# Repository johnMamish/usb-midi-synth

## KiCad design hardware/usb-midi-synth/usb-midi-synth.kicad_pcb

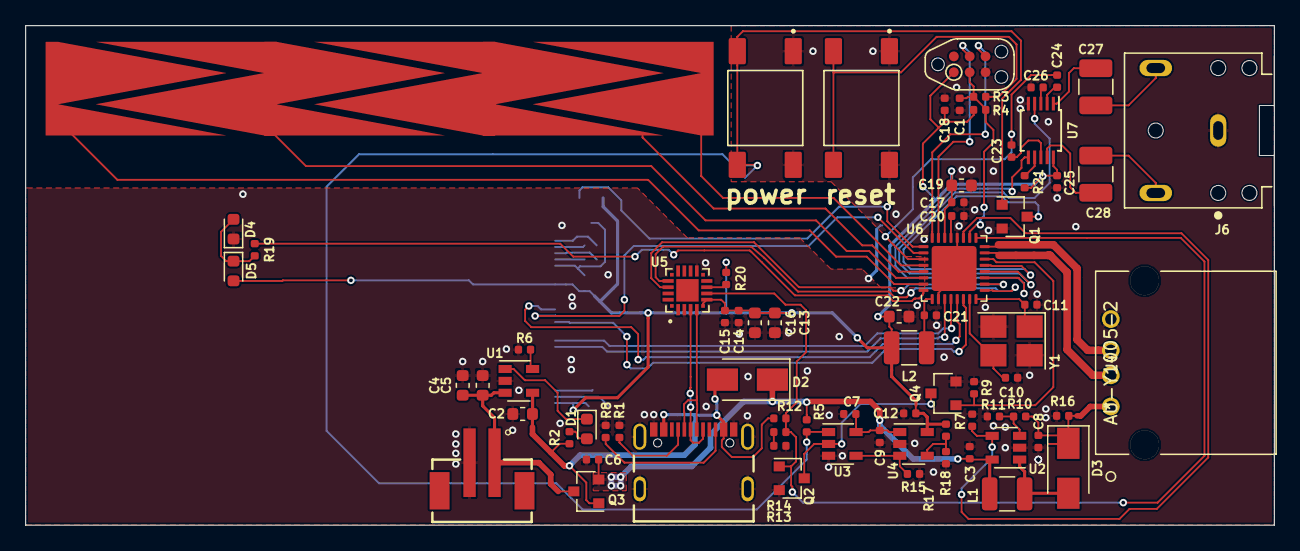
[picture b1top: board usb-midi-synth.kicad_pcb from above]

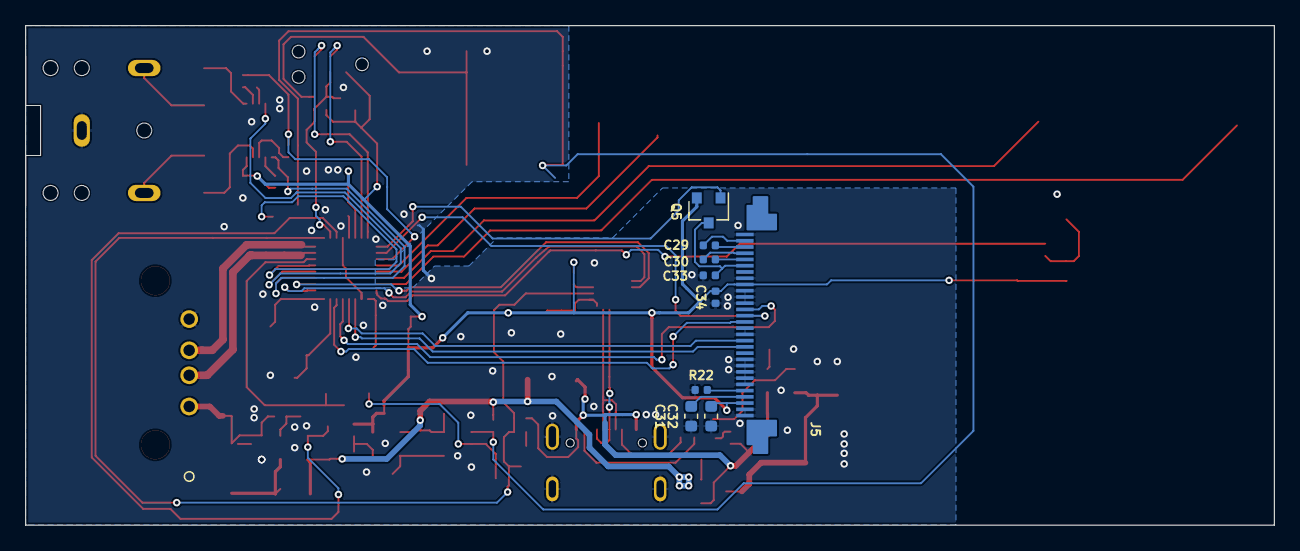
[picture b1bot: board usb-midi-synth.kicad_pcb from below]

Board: 2 copper layers, 100.0 x 40.0 mm, 85 parts (9 on the bottom side), 67 nets.

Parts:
C1, C7, C14, C15, C17, C18, C21: 100n; C_0402_1005Metric
C2, C4, C5, C13, C16, C31: 4.7u; C_0603_1608Metric
C3, C6, C8, C9, C10, C11, C12, C20, C25, C26, C29, C30, C33, C34: 1u; C_0402_1005Metric
C19, C22: 10u; C_0603_1608Metric
C23, C24: 0.47u; C_0402_1005Metric
C27, C28: 47u; C_1210_3225Metric_Pad1.42x2.65mm_HandSolder
C32: 2.2u; C_0603_1608Metric
D1, D4, D5: LED_Small; LED_0603_1608Metric
D2, D3: D; D_SMA
J1: USB4105-GF-A; GCT_USB4105-GF-A
J2: B2B-PH-SM4-TB(LF)(SN); JST_B2B-PH-SM4-TB(LF)(SN)
J3: TC2030-CTX; TC2030-IDC-NL
J4: AU-Y1005-2
J5: Conn_01x30; SFV30R-4STE1HLF
J6: SJ1-3523N; CUI_SJ1-3523N
L1, L2: 10u; L_1210_3225Metric
Q1, Q2, Q4: 2N7002; SOT-23
Q3, Q5: Q_PMOS_GSD; SOT-23
R1, R8: 5.1k; R_0402_1005Metric
R2, R3, R19: 100; R_0402_1005Metric
R4, R5, R7, R9, R11, R12, R13, R14, R15, R18, R20, R21: 10k; R_0402_1005Metric
R6, R16: 2k; R_0402_1005Metric
R10, R17: 30k; R_0402_1005Metric
R22: 390k; R_0402_1005Metric
SW1, SW2: FSM4JSMA; TE_FSM4JSMA
U1: MCP73831-2; SOT-23-5
U2: AP3012K; SOT-23-5
U3: 74AHC1G00; SOT-23-5
U4: ap7366-w5; SOT-23-5
U5: cp2102n-gqfn20; IC_CP2102N-A01-GQFN20
U6: ATSAMD21E18A-M; QFN-32-1EP_5x5mm_P0.5mm_EP3.6x3.6mm
U7: LM4811; TSSOP-10_3x3mm_P0.5mm
UI1: touch-strip; touch-slider-4
Y1: Crystal_GND24; Crystal_SMD_3225-4Pin_3.2x2.5mm_HandSoldering

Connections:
D+_host: J4.3, U6.24
D-_host: J4.2, U6.23
DAC_out: C23.2, C24.2, U6.3
GND: C1.2, C2.2, C3.2, C4.2, C5.2, C6.2, C7.2, C8.2, C9.2, C10.1, C11.1, C12.2, C13.1, C14.1, C15.1, C16.1, C17.2, C18.2, C19.2, C20.1, C21.2, C22.2, C25.1, C26.2, C31.1, C32.1, C33.1, C34.1, D4.1, J1.A1_B12, J1.B1_A12, J1.S1, J1.S2, J1.S3, J1.S4, J2.2, J3.5, J4.4, J5.1, J5.2, J5.6, J5.7, J5.8, J5.9, J5.10, J5.14, J5.15, J5.19, J5.20, J5.21, J5.23, J5.30, J6.1, Q1.2, Q2.2, Q4.2, R1.2, R6.2, R7.2, R8.2, R9.2, R11.2, R14.2, R15.2, R16.1, R18.2, R22.2, SW1.1, SW1.2, SW2.1, SW2.2, U1.2, U2.2, U3.3, U4.2, U5.3, U5.12, U6.10, U6.28, U6.33, U7.5, Y1.2, Y1.4
unnamed: C10.2, U6.15, Y1.3
unnamed: C11.2, U6.16, Y1.1
unnamed: C20.2, U6.29
unnamed: C21.1, L2.1, U6.9
unnamed: C23.1, U7.8
unnamed: C24.1, U7.2
unnamed: C26.1, U7.3
unnamed: C27.1, J6.2
unnamed: C27.2, U7.1
unnamed: C28.1, J6.3
unnamed: C28.2, U7.9
unnamed: C29.1, J5.28
unnamed: C29.2, J5.29
unnamed: C30.1, J5.26
unnamed: C30.2, J5.27
unnamed: C31.2, J5.4
unnamed: C33.2, J5.25, Q5.3
unnamed: D1.1, U1.1
unnamed: D1.2, R2.2
unnamed: D3.2, L1.2, U2.1
unnamed: D4.2, D5.1, R19.2
unnamed: J1.A5, R1.1
unnamed: J1.B5, R8.1
unnamed: J5.5, R22.1
unnamed: Q1.1, R5.2, SW2.3, SW2.4, U3.1
unnamed: Q2.3, Q4.3, U3.2
unnamed: R3.2, SW1.3, SW1.4
unnamed: R6.1, U1.5
unnamed: R10.2, R11.1, U2.3
unnamed: R13.2, R14.1
unnamed: R15.1, U3.4, U4.3
unnamed: R17.2, R18.1, U4.4
unnamed: R19.1, U6.8
unnamed: R20.2, U5.9
unnamed: R21.1, U7.7
VDD: C12.1, C13.2, C14.2, C15.2, C16.2, C17.1, C18.1, C19.1, C22.1, C25.2, C32.2, C34.2, D5.2, J3.1, J5.3, J5.22, L2.2, Q5.2, R4.2, R17.1, R20.1, R21.2, U4.5, U5.6, U5.7, U6.30, U7.10
Vbat: C4.1, C5.1, J2.1, Q3.3, U1.3
Vsys: C3.1, C6.1, C7.1, C9.1, D2.1, L1.1, Q3.2, R5.1, U2.5, U3.5, U4.1
Vusb_device: C2.1, D2.2, J1.A4_B9, J1.B4_A9, Q3.1, R2.1, R12.1, U1.4
Vusb_device_sense: Q2.1, R12.2, R13.1, U5.8, U6.25
Vusb_host: C8.1, D3.1, J4.1, R10.1, R16.2
Vusb_host_enable: R7.1, U2.4, U6.27
disp_copi: J5.12, U6.11
disp_cs: J5.18, U6.13
disp_d-c: J5.16, U6.14
disp_res: J5.17, U6.2
disp_sclk: J5.13, U6.12
disp_vdd_en: Q5.1, U6.1
mcu_ldo_en: Q4.1, R9.1, U6.22
mcu_power_button: Q1.3, U6.21
mcu_reset: C1.1, J3.3, R3.1, R4.1, U6.26
mcu_rx_cp2102_tx: U5.18, U6.18
mcu_swclk: J3.4, U6.31
mcu_swdio: J3.6, U6.32
mcu_tx_cp2102_rx: U5.17, U6.17
slider_1: U6.4, UI1.1
slider_2: U6.5, UI1.2
slider_3: U6.6, UI1.3
slider_4: U6.7, UI1.4
uart_D+: J1.A6, J1.B6, U5.4
uart_D-: J1.A7, J1.B7, U5.5
volume_clock: U6.20, U7.4
volume_up_dn: U6.19, U7.6

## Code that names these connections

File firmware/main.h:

#ifndef _MAIN_H
#define _MAIN_H
#include "samda1e16b.h"
#include <stdint.h>
#include "port.h"

#define FCLK (48000000)

typedef struct systick {
    volatile uint32_t CSR;
    volatile uint32_t RVR;
    volatile uint32_t CVR;
    volatile uint32_t CALIB;
} systick_t;

#define SYSTICK ((volatile systick_t*)0xe000e010)

#define NVIC_ISER ((volatile uint32_t*)0xe000e100)
#define NVIC_ICER ((volatile uint32_t*)0xe000e180)
#define NVIC_ISPR ((volatile uint32_t*)0xe000e200)
#define NVIC_ICPR ((volatile uint32_t*)0xe000e280)
#define NVIC_IPR  ((volatile uint32_t*)0xe000e400)

////////////////////////////////////////////////////////////////
// display pins
const extern gpio_pin_t disp_vdd_en_pin;
const extern gpio_pin_t disp_res_pin;
const extern gpio_pin_t disp_copi_pin;
const extern gpio_pin_t disp_sclk_pin;
const extern gpio_pin_t disp_cs_pin;
const extern gpio_pin_t disp_data_cmd_pin;

////////////////////////////////////////////////////////////////
// DAC pins
const extern gpio_pin_t dac_out_pin;
const extern gpio_pin_t volume_up_dn_pin;
const extern gpio_pin_t volume_clk_pin;

////////////////////////////////////////////////////////////////
// slider pins
const extern gpio_pin_t slider_1_pin;
const extern gpio_pin_t slider_2_pin;
const extern gpio_pin_t slider_3_pin;
const extern gpio_pin_t slider_4_pin;

////////////////////////////////////////////////////////////////
// cp2102 UART pins
const extern gpio_pin_t mcu_tx_cp2102_rx_pin;
const extern gpio_pin_t mcu_tx_cp2102_tx_pin;

////////////////////////////////////////////////////////////////
// power management pins
const extern gpio_pin_t mcu_power_button_pin;
const extern gpio_pin_t mcu_ldo_en_pin;
const extern gpio_pin_t mcu_vusb_host_enable_pin;

////////////////////////////////////////////////////////////////
// usb host pins
const extern gpio_pin_t usb_host_dn;
const extern gpio_pin_t usb_host_dp;

////////////////////////////////////////////////////////////////
// other pins
const extern gpio_pin_t led_hiz_pin;
const extern gpio_pin_t xtal_in_pin;
const extern gpio_pin_t xtal_out_pin;

#endif

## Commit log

2022-06-29 hardware initial commit
2022-06-29 Squashed 'firmware/saeclib/' content from commit dfa403a
    git-subtree-dir: firmware/saeclib
    git-subtree-split: dfa403aeaa6d197b81bfb1e4836d50b807dcd877
2022-06-30 firmware wip
2022-09-11 usb enum issue wip
2022-12-04 a bunch of code idk synthesis works now
2022-12-04 add a bunch of random prototyping / test code
2023-01-06 BLIT waveform generation passes smoke test; tester in tools/cli_player

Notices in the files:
parts and their libraries:
Copyright 2021 Accelerated Designs. All rights reserved.
